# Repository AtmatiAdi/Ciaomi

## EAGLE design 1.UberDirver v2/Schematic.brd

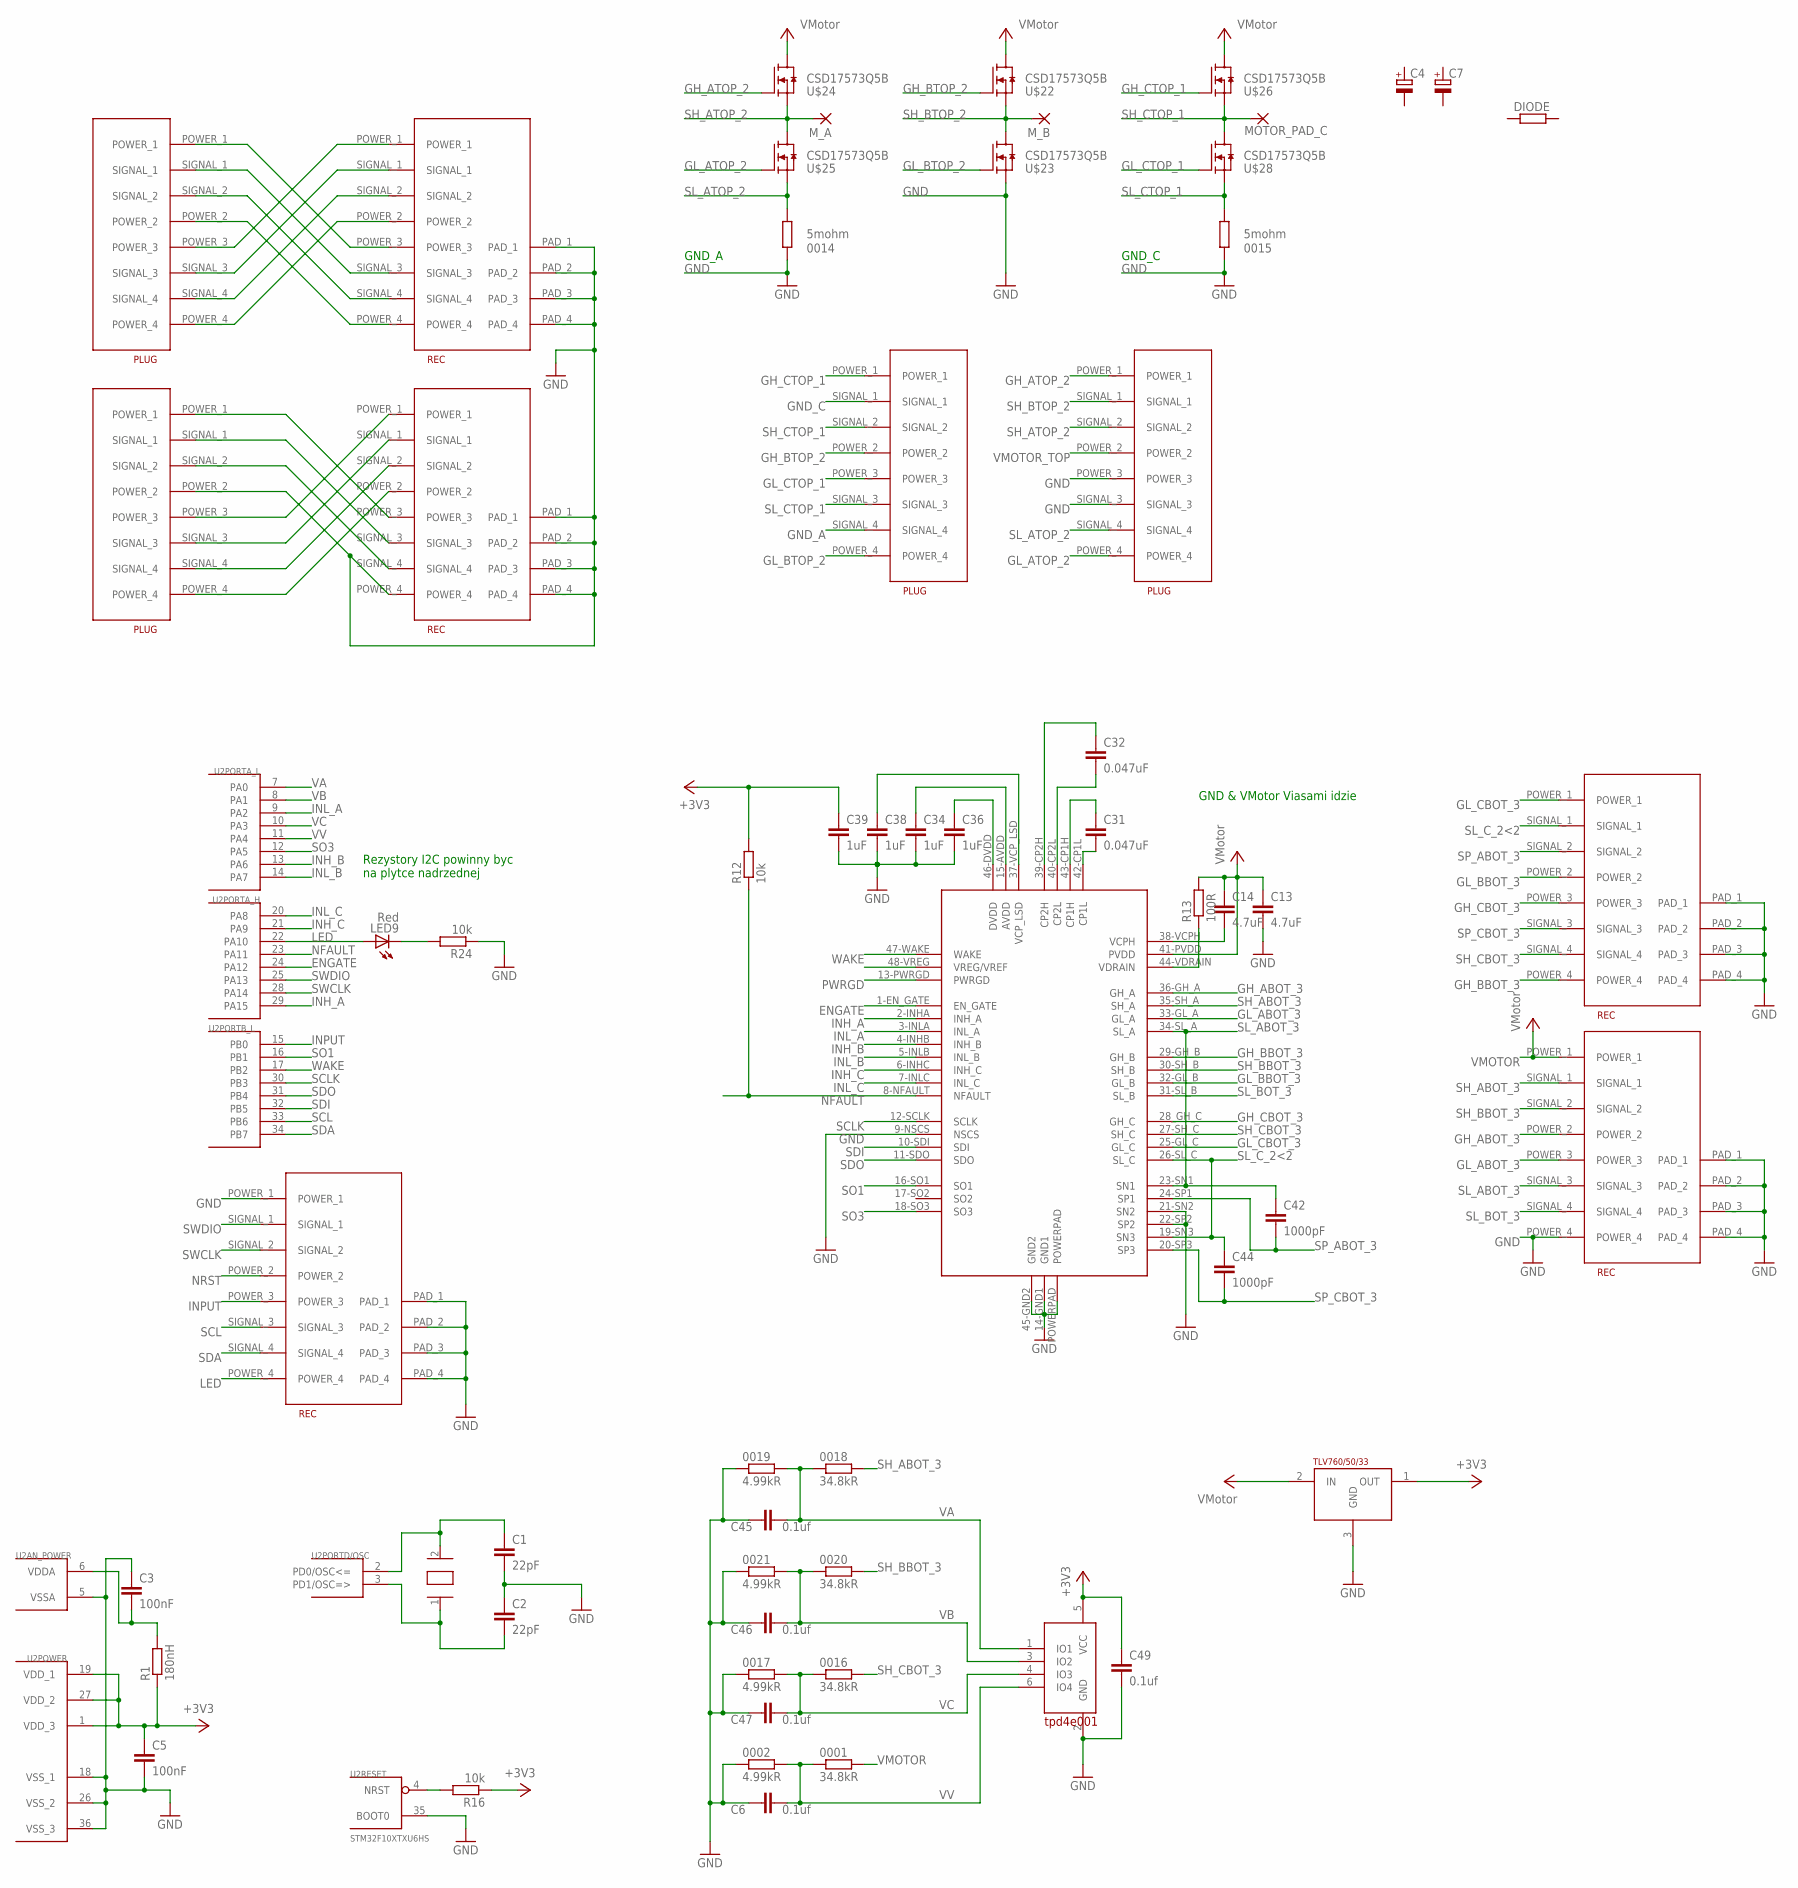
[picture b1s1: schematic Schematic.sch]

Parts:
0001, 0016, 0018, 0020: 34.8kR; R0603
0002, 0017, 0019, 0021: 4.99kR; R0603
0014, 0015: 5mohm; R2512
C1, C2: 22pF; C0603
C3, C5: 100nF; C0603
C4, C7: CPOL-EU153CLV-0807; 153CLV-0807
C6, C45, C46, C47, C49: 0.1uf; C0603
C13, C14: 4.7uF; C0805
C31, C32: 0.047uF; C0603
C34, C36, C38, C39: 1uF; C0603
C42, C44: 1000pF; C0603
DIODE: R-EU_R0805; R0805
LED9: Red; SML0603
MOTOR_PAD_C: SMD5; SMD2,54-5,08
M_A: SMD5; SMD2,54-5,08
M_B: SMD5; SMD2,54-5,08
R1: 180nH; R0603
R12, R16, R24: 10k; R0603
R13: 100R; R0603
U2: STM32F10XTXU6HS; VFQFPN36-HS
U$1, U$2, U$4, U$5, U$9: MOLEG_REC_8X0.4MM; REC
U$3, U$6, U$7, U$8: MOLEX_PLUG_8X0.4MM; PLUG
U$10: OSC_8MHZ; SMD_MINI
U$11: TLV760XX; SOT-23-3
U$21: DRV8305; S-PQFP-G48
U$22, U$23, U$24, U$25, U$26, U$28: CSD17573Q5B; Q5B
U$31: TPD4E001; SOT-23

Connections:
+3V3: C5.1, C39.1, C49.1, R1.1, R12.2, R16.1, U2.1 (VDD_3), U2.19 (VDD_1), U2.27 (VDD_2), U$11.1 (OUT), U$31.5 (VCC)
ENGATE: U2.24 (PA12), U$21.1-EN_GATE (EN_GATE)
GH_ABOT_3: U$9.POWER_2, U$21.36-GH_A (GH_A)
GH_ATOP_2: U$3.POWER_1, U$24.G
GH_BBOT_3: U$4.POWER_4, U$21.29-GH_B (GH_B)
GH_BTOP_2: U$6.POWER_2, U$22.G
GH_CBOT_3: U$4.POWER_3, U$21.28_GH_C (GH_C)
GH_CTOP_1: U$6.POWER_1, U$26.G
GL_ABOT_3: U$9.POWER_3, U$21.33-GL_A (GL_A)
GL_ATOP_2: U$3.POWER_4, U$25.G
GL_BBOT_3: U$4.POWER_2, U$21.32-GL_B (GL_B)
GL_BTOP_2: U$6.POWER_4, U$23.G
GL_CBOT_3: U$4.POWER_1, U$21.25-GL_C (GL_C)
GL_CTOP_1: U$6.POWER_3, U$28.G
GND: 0002.1, 0014.1, 0015.1, 0017.1, 0019.1, 0021.1, C1.2, C2.1, C3.1, C5.2, C6.2, C13.2, C34.2, C36.2, C38.2, C39.2, C45.2, C46.2, C47.2, C49.2, R24.1, U2.5 (VSSA), U2.18 (VSS_1), U2.26 (VSS_2), U2.35 (BOOT0), U2.36 (VSS_3), U$1.PAD_1, U$1.PAD_2, U$1.PAD_3, U$1.PAD_4, U$2.PAD_1, U$2.PAD_2, U$2.PAD_3, U$2.PAD_4, U$2.POWER_1, U$3.POWER_3, U$3.SIGNAL_3, U$4.PAD_1, U$4.PAD_2, U$4.PAD_3, U$4.PAD_4, U$5.PAD_1, U$5.PAD_2, U$5.PAD_3, U$5.PAD_4, U$5.POWER_4, U$8.POWER_2, U$9.PAD_1, U$9.PAD_2, U$9.PAD_3, U$9.PAD_4, U$9.POWER_4, U$11.3 (GND), U$21.9-NSCS (NSCS), U$21.14-GND1 (GND1), U$21.21-SN2 (SN2), U$21.22-SP2 (SP2), U$21.45-GND2 (GND2), U$21.POWERPAD, U$23.S1 (S), U$23.S2 (S), U$23.S3 (S), U$31.2 (GND)
GND_A: U$6.SIGNAL_4
GND_C: U$6.SIGNAL_1
INH_A: U2.29 (PA15), U$21.2-INHA (INH_A)
INH_B: U2.13 (PA6), U$21.4-INHB (INH_B)
INH_C: U2.21 (PA9), U$21.6-INHC (INH_C)
INL_A: U2.9 (PA2), U$21.3-INLA (INL_A)
INL_B: U2.14 (PA7), U$21.5-INLB (INL_B)
INL_C: U2.20 (PA8), U$21.7-INLC (INL_C)
INPUT: U2.15 (PB0), U$2.POWER_3
LED: LED9.A, U2.22 (PA10), U$2.POWER_4
unnamed: U$5.POWER_3, U$8.POWER_1
unnamed: U$5.SIGNAL_3, U$8.SIGNAL_1
unnamed: U$5.SIGNAL_4, U$8.SIGNAL_2
unnamed: U$1.POWER_3, U$7.POWER_1
unnamed: U$1.SIGNAL_3, U$7.SIGNAL_1
unnamed: U$1.SIGNAL_4, U$7.SIGNAL_2
unnamed: C36.1, U$21.46-DVDD (DVDD)
unnamed: U$1.POWER_4, U$7.POWER_2
unnamed: C34.1, U$21.15-AVDD (AVDD)
unnamed: C38.1, U$21.37-VCP_LSD (VCP_LSD)
unnamed: C31.2, U$21.42-CP1L (CP1L)
unnamed: U$5.POWER_1, U$8.POWER_3
unnamed: C31.1, U$21.43-CP1H (CP1H)
unnamed: U$5.SIGNAL_1, U$8.SIGNAL_3
unnamed: U$5.SIGNAL_2, U$8.SIGNAL_4
unnamed: U$5.POWER_2, U$8.POWER_4
unnamed: C32.2, U$21.40-CP2L (CP2L)
unnamed: C32.1, U$21.39-CP2H (CP2H)
unnamed: R13.1, U$21.44-VDRAIN (VDRAIN)
unnamed: C14.2, U$21.38-VCPH (VCPH)
unnamed: C1.1, U2.2 (PD0/OSC<=), U$10.2
unnamed: U$1.POWER_1, U$7.POWER_3
unnamed: U$1.SIGNAL_1, U$7.SIGNAL_3
unnamed: U$1.SIGNAL_2, U$7.SIGNAL_4
unnamed: U$1.POWER_2, U$7.POWER_4
unnamed: C3.2, R1.2, U2.6 (VDDA)
unnamed: C2.2, U2.3 (PD1/OSC=>), U$10.1
unnamed: LED9.C, R24.2
NFAULT: R12.1, U2.23 (PA11), U$21.8-NFAULT (NFAULT)
NRST: R16.2, U2.4 (NRST), U$2.POWER_2
PWRGD: U$21.13-PWRGD (PWRGD)
SCL: U2.33 (PB6), U$2.SIGNAL_3
SCLK: U2.30 (PB3), U$21.12-SCLK (SCLK)
SDA: U2.34 (PB7), U$2.SIGNAL_4
SDI: U2.32 (PB5), U$21.10-SDI (SDI)
SDO: U2.31 (PB4), U$21.11-SDO (SDO)
SH_ABOT_3: 0018.2, U$9.SIGNAL_1, U$21.35-SH_A (SH_A)
SH_ATOP_2: M_A.1, U$3.SIGNAL_2, U$24.S1 (S), U$24.S2 (S), U$24.S3 (S), U$25.D1 (D), U$25.D2 (D), U$25.D3 (D), U$25.D4 (D), U$25.D5 (D)
SH_BBOT_3: 0020.2, U$9.SIGNAL_2, U$21.30-SH_B (SH_B)
SH_BTOP_2: M_B.1, U$3.SIGNAL_1, U$22.S1 (S), U$22.S2 (S), U$22.S3 (S), U$23.D1 (D), U$23.D2 (D), U$23.D3 (D), U$23.D4 (D), U$23.D5 (D)
SH_CBOT_3: 0016.2, U$4.SIGNAL_4, U$21.27-SH_C (SH_C)
SH_CTOP_1: MOTOR_PAD_C.1, U$6.SIGNAL_2, U$26.S1 (S), U$26.S2 (S), U$26.S3 (S), U$28.D1 (D), U$28.D2 (D), U$28.D3 (D), U$28.D4 (D), U$28.D5 (D)
SL_ABOT_3: C42.1, U$9.SIGNAL_3, U$21.23-SN1 (SN1), U$21.34-SL_A (SL_A)
SL_ATOP_2: 0014.2, U$3.SIGNAL_4, U$25.S1 (S), U$25.S2 (S), U$25.S3 (S)
SL_BOT_3: U$9.SIGNAL_4, U$21.31-SL_B (SL_B)
SL_CTOP_1: 0015.2, U$6.SIGNAL_3, U$28.S1 (S), U$28.S2 (S), U$28.S3 (S)
SL_C_2<2: C44.1, U$4.SIGNAL_1, U$21.19-SN3 (SN3), U$21.26-SL_C (SL_C)
SO1: U2.16 (PB1), U$21.16-SO1 (SO1)
SO3: U2.12 (PA5), U$21.18-SO3 (SO3)
SP_ABOT_3: C42.2, U$4.SIGNAL_2, U$21.24-SP1 (SP1)
SP_CBOT_3: C44.2, U$4.SIGNAL_3, U$21.20-SP3 (SP3)
SWCLK: U2.28 (PA14), U$2.SIGNAL_2
SWDIO: U2.25 (PA13), U$2.SIGNAL_1
VA: 0018.1, 0019.2, C45.1, U2.7 (PA0), U$31.1 (IO1)
VB: 0020.1, 0021.2, C46.1, U2.8 (PA1), U$31.3 (IO2)
VC: 0016.1, 0017.2, C47.1, U2.10 (PA3), U$31.4 (IO3)
VMOTOR: 0001.2, C13.1, C14.1, R13.2, U$9.POWER_1, U$11.2 (IN), U$21.41-PVDD (PVDD)
VMOTOR_TOP: U$3.POWER_2, U$22.D1 (D), U$22.D2 (D), U$22.D3 (D), U$22.D4 (D), U$22.D5 (D), U$24.D1 (D), U$24.D2 (D), U$24.D3 (D), U$24.D4 (D), U$24.D5 (D), U$26.D1 (D), U$26.D2 (D), U$26.D3 (D), U$26.D4 (D), U$26.D5 (D)
VV: 0001.1, 0002.2, C6.1, U2.11 (PA4), U$31.6 (IO4)
WAKE: U2.17 (PB2), U$21.47-WAKE (WAKE)

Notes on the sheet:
GND & VMotor Viasami idzie
Rezystory I2C powinny byc na plytce nadrzednej
GND_A
GND_C

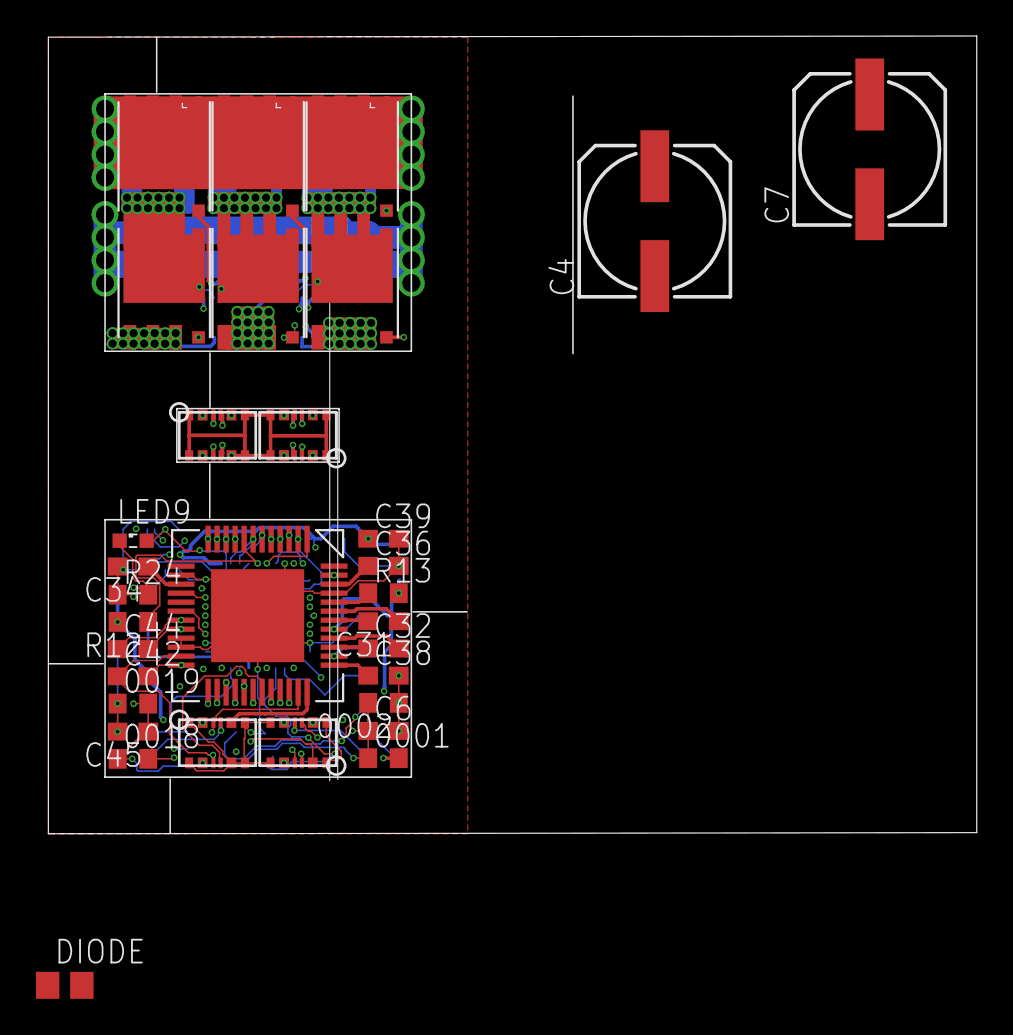
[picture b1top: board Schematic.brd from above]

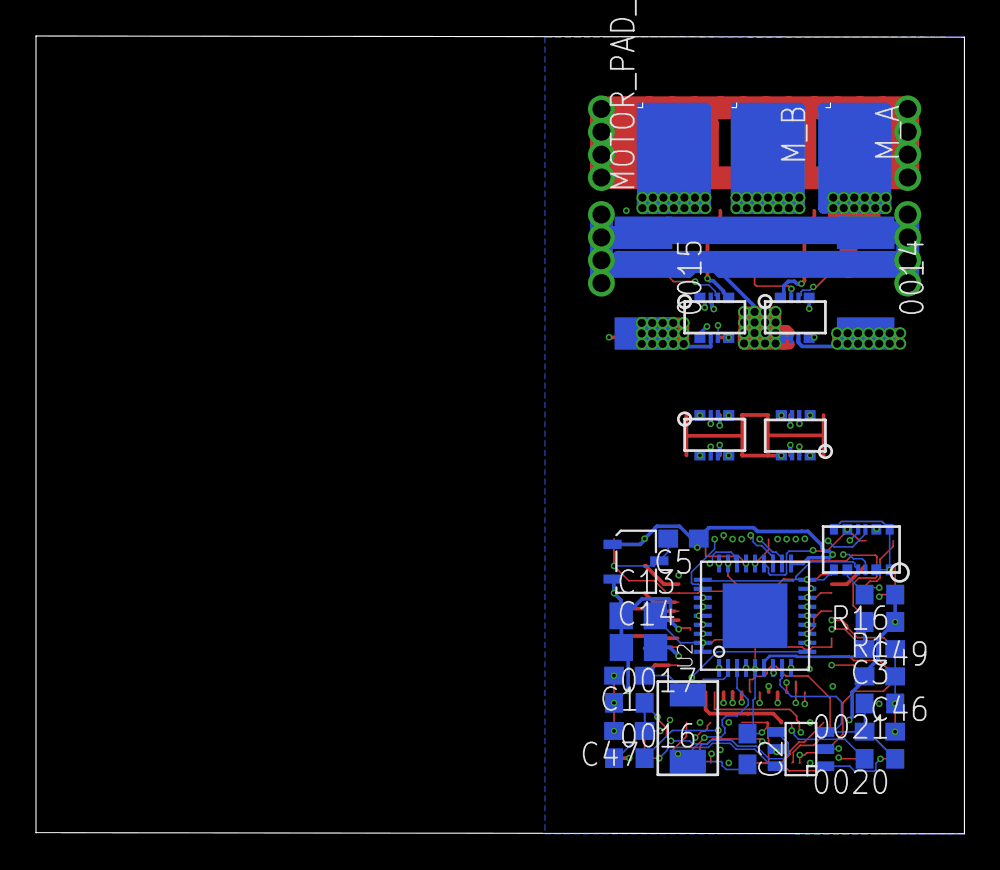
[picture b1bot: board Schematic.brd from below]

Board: 4 copper layers, 51.5 x 44.3 mm, 61 parts (29 on the bottom side), 82 nets.

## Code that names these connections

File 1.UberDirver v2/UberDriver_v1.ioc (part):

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Mcu.Name=STM32F103T(8-B)Ux
Mcu.Package=VFQFPN36
Mcu.UserName=STM32F103TBUx
PA0-WKUP.Signal=ADCx_IN0
PA1.Signal=ADCx_IN1
PA10.GPIOParameters=GPIO_Label
PA10.GPIO_Label=LED
PA10.Signal=GPIO_Output
PA11.GPIOParameters=GPIO_Label
PA11.GPIO_Label=NFAULT
PA11.Signal=GPIO_Input
PA12.GPIOParameters=GPIO_Label
PA12.GPIO_Label=ENGATE
PA12.Signal=GPIO_Output
PA13.Mode=Serial_Wire
PA13.Signal=SYS_JTMS-SWDIO
PA14.Mode=Serial_Wire
PA14.Signal=SYS_JTCK-SWCLK
PA15.Signal=S_TIM2_CH1_ETR
PA2.Signal=S_TIM2_CH3
PA3.Signal=ADCx_IN3
PA4.Signal=ADCx_IN4
PA5.Signal=ADCx_IN5
PA6.Signal=S_TIM3_CH1
PA7.Signal=S_TIM3_CH2
PA8.Signal=S_TIM1_CH1
PA9.Signal=S_TIM1_CH2
PB0.Signal=ADCx_IN8
PB1.Signal=ADCx_IN9
PB2.GPIOParameters=GPIO_Label
PB2.GPIO_Label=WAKE
PB2.Signal=GPIO_Output
PB3.Mode=Full_Duplex_Master
PB3.Signal=SPI1_SCK
PB4.Mode=Full_Duplex_Master
PB4.Signal=SPI1_MISO
PB5.Mode=Full_Duplex_Master
PB5.Signal=SPI1_MOSI
PB6.Mode=I2C
PB6.Signal=I2C1_SCL
PB7.Mode=I2C
PB7.Signal=I2C1_SDA
PD0-OSC_IN.Mode=HSE-External-Oscillator
PD0-OSC_IN.Signal=RCC_OSC_IN
PD1-OSC_OUT.Mode=HSE-External-Oscillator
PD1-OSC_OUT.Signal=RCC_OSC_OUT
RCC.SYSCLKFreq_VALUE=64000000
RCC.SYSCLKSource=RCC_SYSCLKSOURCE_PLLCLK

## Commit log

2020-05-14 Wprowadzono projekt
2020-07-01 Zdjęcia
